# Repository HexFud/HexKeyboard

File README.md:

# 9-key macropad + encoder + OLED

Homemade macropad: 9 keys in a 3x3 grid, a rotary encoder, and a 0.91" OLED screen. Every switch has its own RGB LED for backlighting, all chained together on a single data pin.

## Hardware

- Seeed XIAO RP2040
- 0.91 inch OLED display
- Rotary encoder with built-in push button
- 9x MX-Style switches, each with its own 1N4148 diode, 3x3 matrix
- 9x SK6812MINI-E LEDs daisy-chained for per-key backlighting

## Schematic

## PCB Render

## PCB

## Case

## Case Heated Inserts

You can put heated inserts in the highlited zones and then screw the pcb in 

## BOM

| Qty | Part | Notes |
|---|---|---|
| 1 | Seeed XIAO RP2040 | main MCU |
| 1 | 0.91 inch OLED display | SSD1306 driver |
| 1 | Rotary encoder |
| 9 | Mechanical switches (MX-style) | |
| 9 | SK6812MINI-E RGB LED | daisy-chained backlight |
| 10 | 1N4148 diode | 9 for the key matrix + 1 for the encoder push button |
| 9 | Keycaps | |
| — | Case (top plate + bottom plate) | 3D printed |
| 8 | M3x16mm screws |
| 4 | M3x5x4mm heatset inserts |

## Firmware 

1. Flash CircuitPython onto the XIAO
2. Clone the KMK library (github.com/KMKfw/kmk_firmware) and copy its kmk/ folder onto the CIRCUITPY drive. Also install these CircuitPython libraries onto the board: adafruit_display_text, adafruit_displayio_ssd1306.
3. Copy boot.py and code.py to the root of the CIRCUITPY drive.
4. Reset the board (boot.py only runs on reset/power-up, not on save).

## What it does

- 9 programmable keys
- Encoder: function described below
- Screen: shows the progress bar of whatever track is playing 
- Per key RGB backlighting

## The music bar
 
I implemented a feature called music bar, if you are playing something in the background the duration of the media is showed on the display and you can controll it with the encoder. If you want to use this function you need to run the .py program in the firmware folder because otherwise the microcontroller doesn't know what is the device playing

## Note

The push button of the encoder is intentionally disconnected because there were no pins left on the microcontroller to connect it

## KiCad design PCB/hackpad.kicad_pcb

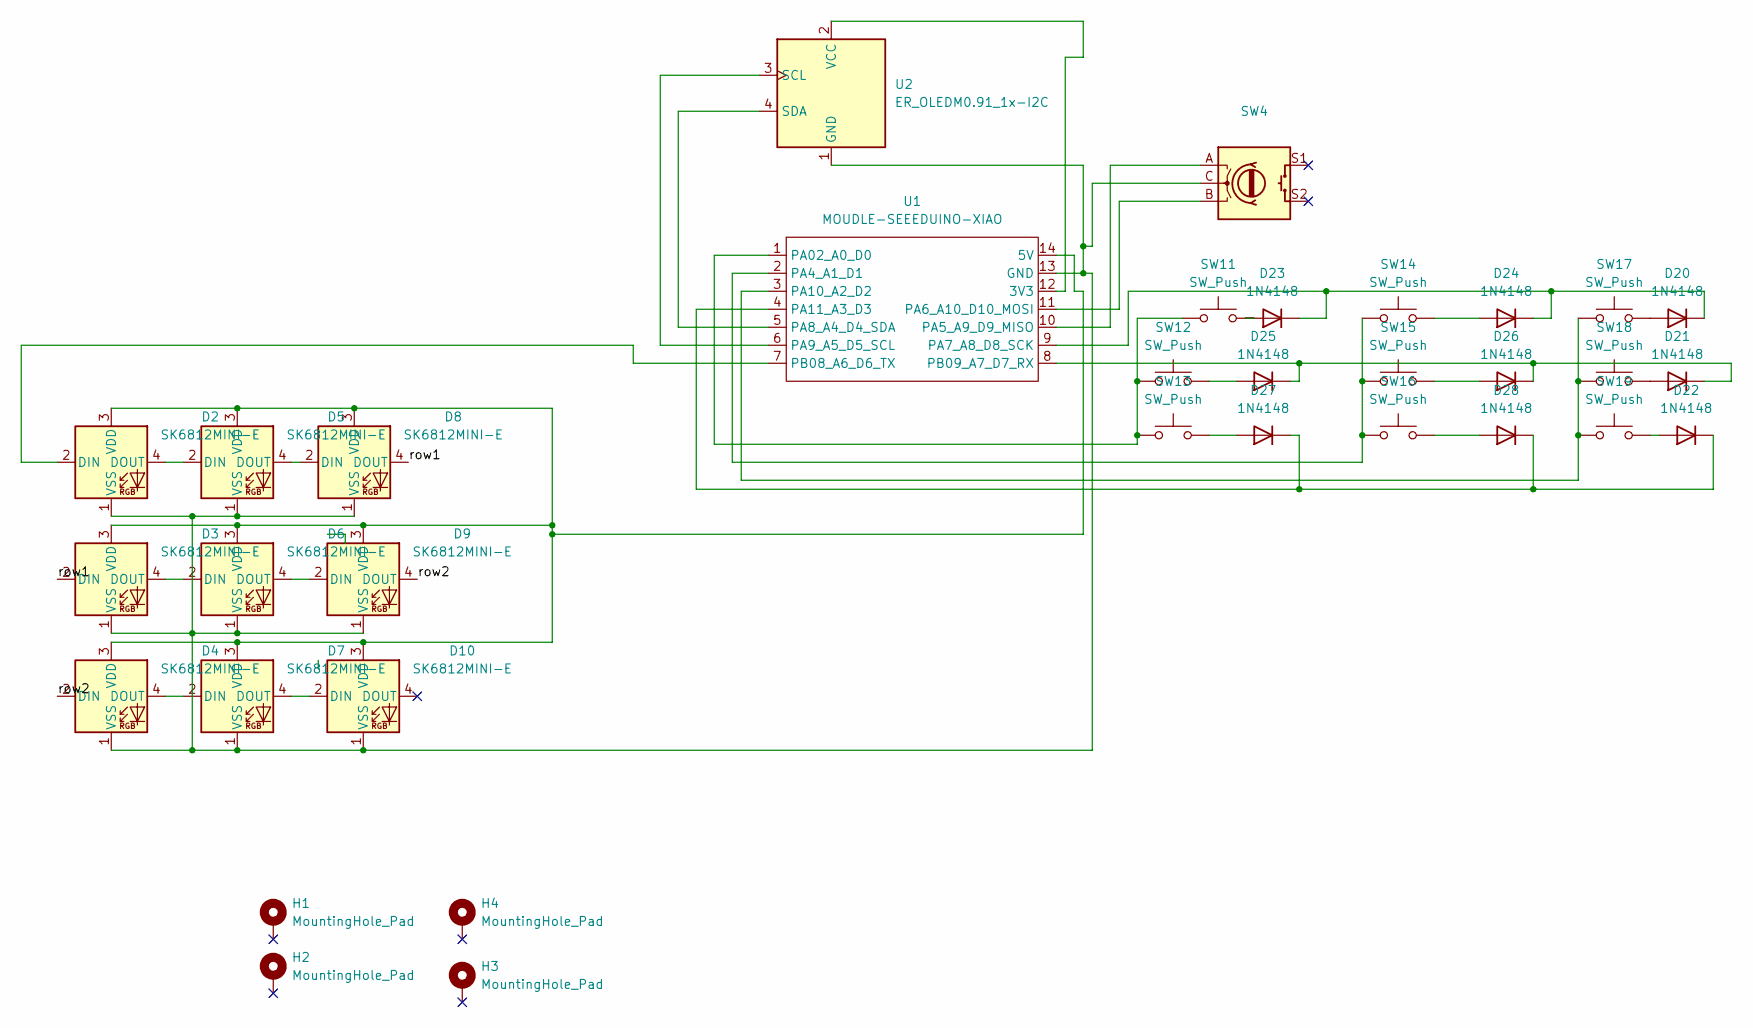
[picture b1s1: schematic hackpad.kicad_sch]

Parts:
D2, D3, D4, D5, D6, D7, D8, D9, D10: SK6812MINI-E; LED_SK6812MINI-E_3.2x2.8mm_P1.5mm_ReverseMount
D20, D21, D22, D23, D24, D25, D26, D27, D28: 1N4148; D_DO-35_SOD27_P7.62mm_Horizontal
H1, H2, H3, H4: MountingHole_Pad; MountingHole_3.2mm_M3_Pad_Via
SW4: RotaryEncoder_Switch; RotaryEncoder_Alps_EC11E-Switch_Vertical_H20mm
SW11, SW12, SW13, SW14, SW15, SW16, SW17, SW18, SW19: SW_Push; SW_Cherry_MX_1.00u_PCB
U1: MOUDLE-SEEEDUINO-XIAO; XIAO-Generic-Hybrid-14P-2.54-21X17.8MM
U2: ER_OLEDM0.91_1x-I2C; SSD1306-0.91-OLED-4pin-128x32

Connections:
/row1: D3.2 (DIN), D8.4 (DOUT)
/row2: D4.2 (DIN), D9.4 (DOUT)
unnamed: D2.2 (DIN), U1.7 (PB08_A6_D6_TX)
unnamed: D2.4 (DOUT), D5.2 (DIN)
unnamed: D3.4 (DOUT), D6.2 (DIN)
unnamed: D4.4 (DOUT), D7.2 (DIN)
unnamed: D5.4 (DOUT), D8.2 (DIN)
unnamed: D6.4 (DOUT), D9.2 (DIN)
unnamed: D7.4 (DOUT), D10.2 (DIN)
unnamed: D2.3 (VDD), D3.3 (VDD), D4.3 (VDD), D5.3 (VDD), D6.3 (VDD), D7.3 (VDD), D8.3 (VDD), D9.3 (VDD), D10.3 (VDD), U1.14 (5V)
unnamed: D2.1 (VSS), D3.1 (VSS), D4.1 (VSS), D5.1 (VSS), D6.1 (VSS), D7.1 (VSS), D8.1 (VSS), D9.1 (VSS), D10.1 (VSS), SW4.C, U1.13 (GND), U2.1 (GND)
unnamed: D20.2 (A), SW17.2
unnamed: D20.1 (K), D23.1 (K), D24.1 (K), U1.9 (PA7_A8_D8_SCK)
unnamed: D21.2 (A), SW18.2
unnamed: D21.1 (K), D25.1 (K), D26.1 (K), U1.8 (PB09_A7_D7_RX)
unnamed: D22.2 (A), SW19.2
unnamed: D22.1 (K), D27.1 (K), D28.1 (K), U1.4 (PA11_A3_D3)
unnamed: D23.2 (A), SW11.2
unnamed: D24.2 (A), SW14.2
unnamed: D25.2 (A), SW12.2
unnamed: D26.2 (A), SW15.2
unnamed: D27.2 (A), SW13.2
unnamed: D28.2 (A), SW16.2
unnamed: U1.12 (3V3), U2.2 (VCC)
unnamed: SW11.1, SW12.1, SW13.1, U1.1 (PA02_A0_D0)
unnamed: SW14.1, SW15.1, SW16.1, U1.2 (PA4_A1_D1)
unnamed: SW4.A, U1.10 (PA5_A9_D9_MISO)
unnamed: SW4.B, U1.11 (PA6_A10_D10_MOSI)
unnamed: U1.5 (PA8_A4_D4_SDA), U2.4 (SDA)
unnamed: U1.6 (PA9_A5_D5_SCL), U2.3 (SCL)
unnamed: SW17.1, SW18.1, SW19.1, U1.3 (PA10_A2_D2)

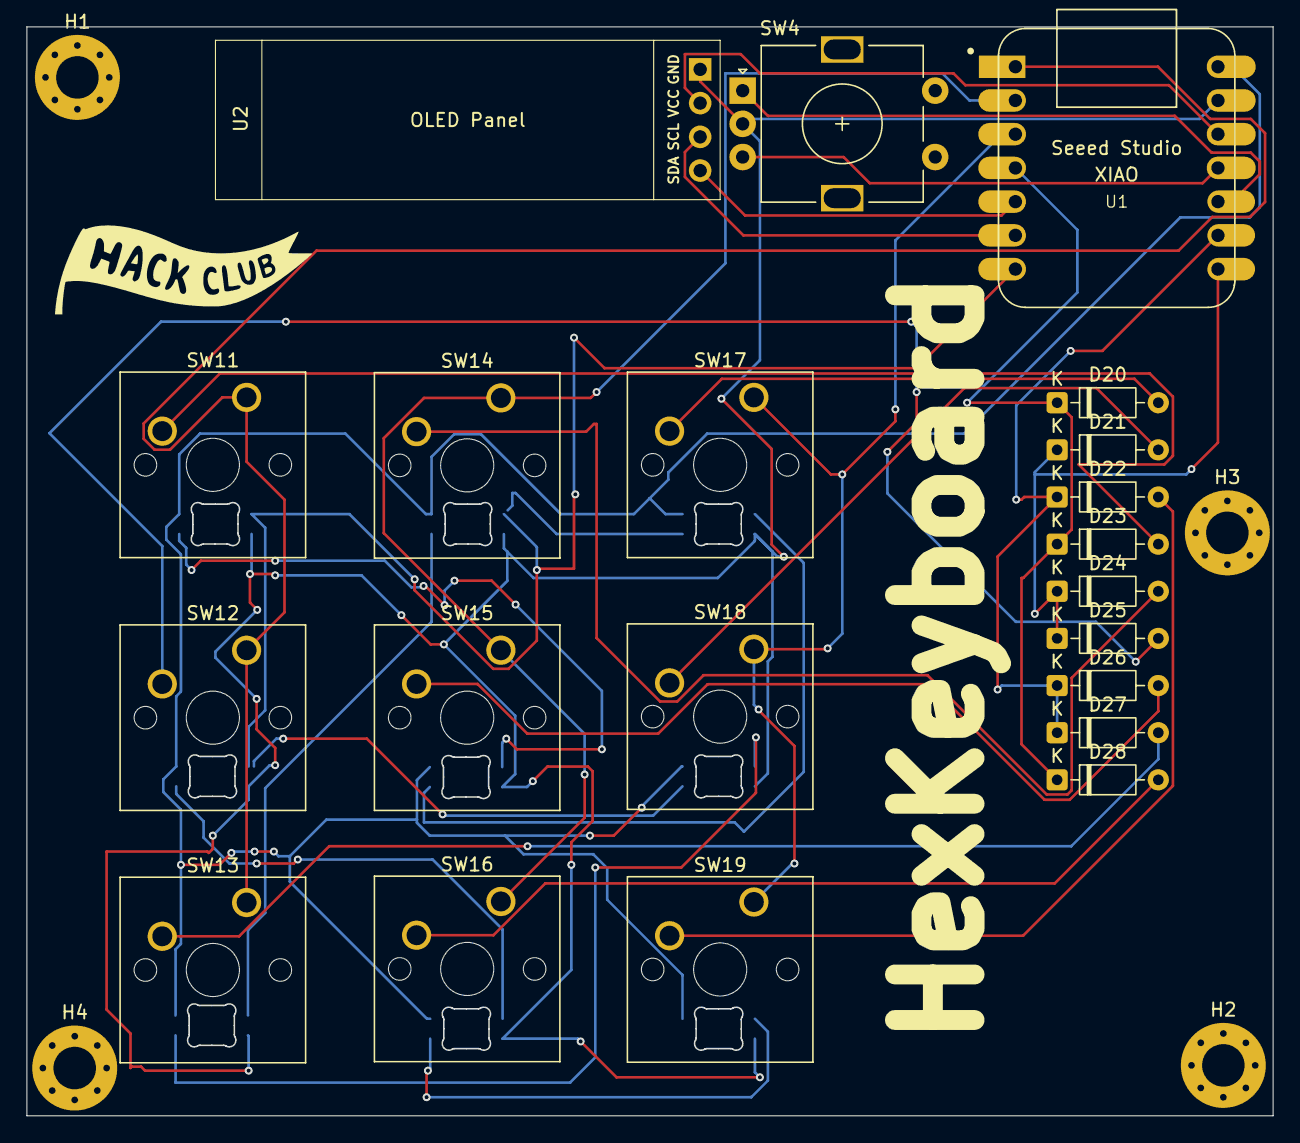
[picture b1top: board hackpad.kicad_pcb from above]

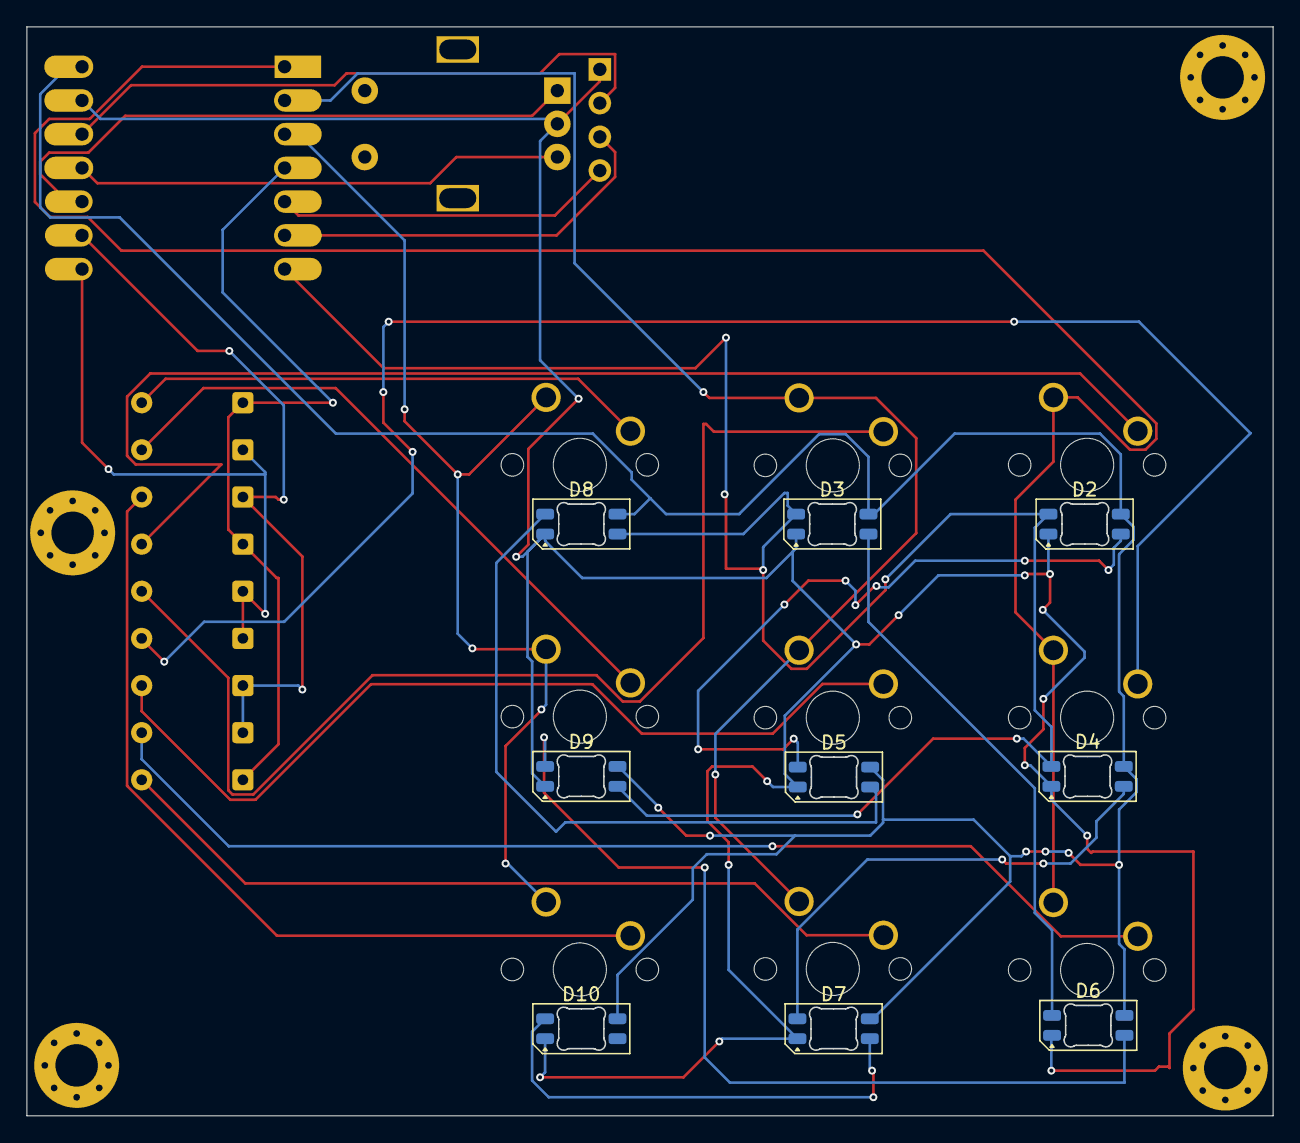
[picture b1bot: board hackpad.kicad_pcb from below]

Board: 2 copper layers, 93.8 x 82.0 mm, 34 parts (9 on the bottom side), 31 nets.
